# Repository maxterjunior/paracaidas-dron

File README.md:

# Paracaídas de Emergencia para DJI Matrice 400

Sistema autónomo que detecta la caída libre del dron con una IMU y despliega un paracaídas mediante un tubo de muelle. Funciona **independiente del flight controller**: tiene su propia batería, su MCU y su sensor.

<p align="center">

</p>
<p align="center"><sub>Izquierda: mecanismo en el <a href="https://claude.ai/artifact/HH7TuvKMzHhvBDsvPzRwz9">visor 3D</a>. Derecha: placa de control (render de KiCad).</sub></p>

| | |
|---|---|
| **Dron objetivo** | DJI Matrice 400: 9.74 kg con baterías, MTOW 15.8 kg |
| **MCU** | PIC18F25K22 (SSOP-28) con oscilador interno de 16 MHz sin PLL, 3.3 V |
| **IMU** | BMI088 (acelerómetro ±12 g + giróscopo ±1000 °/s) soldado en la placa, I²C: acel. 0x18 / giro 0x68 |
| **Actuador** | Solenoide 5 V que libera el pestillo de un tubo de muelle |
| **Mecanismo** | Tubo Ø100 × 280 mm con tapa articulada, modelo paramétrico OpenSCAD y [visor 3D](https://claude.ai/artifact/HH7TuvKMzHhvBDsvPzRwz9) |
| **Paracaídas** | Circular, ripstop nylon 30D, **Ø3.5 m**, 12 gajos, descenso ≤ 6 m/s a 16 kg |
| **Alimentación** | LiPo 1S 1000 mAh → interruptor MOSFET → LDO 3.3 V (XC6206) + boost 5.1 V (MT3608) |

## Estado

| Área | Estado |
|---|---|
| Investigación de módulos y paracaídas | ✅ Completa |
| Esquemático (KiCad 10, rev. v4, todo SMD) | ✅ Cableado, ERC limpio, campo LCSC en cada componente |
| PCB 2 capas 60 × 40 mm | ✅ Ruteado, planos de GND, DRC limpio, archivos JLCPCB listos |
| Firmware (MPLAB XC8) | 🚧 v0.1.0 escrita, sin compilar ni probar en hardware |
| Mecanismo (tubo de muelle) | 🚧 Modelo 3D y STL listos, sin interferencias; faltan medidas reales del solenoide y del montaje en el M400 |
| Canopia | ⏳ Pendiente (comprar o coser, ver `modulos.md`) |

## Cómo funciona

```
LiPo 1S ─Q3/SW1─┬─► XC6206 3.3V ─► PIC18F25K22 ◄─I²C─► BMI088
                │                       │
                └─► MT3608 5.1V ────────┼─► AO3400A ─► Solenoide ─► pestillo ─► muelle ─► paracaídas
                                        └─► LEDs / buzzer
```

1. El PIC lee el BMI088 a 500 Hz y filtra las señales con IIR de primer orden (solo aritmética entera, el PIC18 no tiene FPU).
2. Se **arma** solo en vuelo: cuando detecta la vibración de los motores durante 5 s. En tierra no dispara.
3. Armado, despliega si se cumple cualquiera de estos criterios: **caída libre** (|a| < 0.3 g durante 100 ms), **giro descontrolado** (|ω| > 250 °/s durante 300 ms) o **inclinación** (> 70° durante 500 ms).
4. Da dos pulsos de 300 ms al solenoide, que retrae el émbolo que bloquea la palanca del pestillo. La tapa se abre y el muelle expulsa el paracaídas en ~50–100 ms (ver [Mecanismo](#mecanismo)).
5. El pestillo retiene **sin energía**. Un reset nunca despliega por sí solo (R2 mantiene Q1 apagado), pero si el PIC se reinicia *durante* un despliegue, lo repite al arrancar.

Detalles en [`firmware/README.md`](firmware/README.md).

### Limitaciones conocidas

- **Altura mínima de despliegue: ~20–40 m.** Entre detección, expulsión e inflado se pierden 1.5–2.5 s.
- **La caída libre sola no basta.** Si falla un motor, el dron gira con los demás empujando y el acelerómetro no ve 0 g. Por eso el firmware también dispara por giro e inclinación. Falta un disparo manual por radio (RB2 libre) y calibrar los umbrales con vuelos reales.
- **No corta los motores.** El tubo debe expulsar hacia arriba, fuera del plano de las hélices.

## Estructura del repositorio

```
paracaidas-dron/
├── docs/
│   ├── esquematicos/esquematico.md   # Fuente de verdad: componentes, netlist pin a pin, notas
│   └── investigacion/modulos.md      # Selección de módulos, cálculo y construcción del paracaídas
├── hardware/
│   ├── paracaidas-matrice400/        # Proyecto KiCad 10 (.kicad_pro / .kicad_sch / .kicad_pcb)
│   │   ├── paracaidas.kicad_sym      # Símbolo propio (BMI088 en modo I2C)
│   │   ├── paracaidas.pretty/        # Footprint propio (buzzer MLT-9650)
│   │   └── jlcpcb/                   # Gerbers, BOM y CPL para pedir la placa armada
│   └── mecanismo/
│       ├── mecanismo.scad            # Modelo paramétrico OpenSCAD (tubo, tapa, pestillo, caja, adaptador)
│       ├── stl/                      # Piezas imprimibles exportadas
│       └── visor/                    # Visor 3D (three.js) generado desde los STL
├── firmware/                         # PIC18F25K22, MPLAB XC8 (ver firmware/README.md)
│   ├── src/                          # main, detector, configuración, placa
│   ├── lib/                          # HAL (tick, I2C, UART, ADC) y driver BMI088
│   └── test/                         # pruebas de la lógica de detección en la PC
├── CLAUDE.md                         # Guía para Claude Code
└── README.md
```

## Primeros pasos

### Abrir el hardware

1. Instala [KiCad 10](https://www.kicad.org/download/).
2. Abre `hardware/paracaidas-matrice400/paracaidas-matrice400.kicad_pro`.

Para verificar el diseño desde la línea de comandos:

```sh
KICAD="C:/Program Files/KiCad/10.0/bin/kicad-cli.exe"
cd hardware/paracaidas-matrice400

"$KICAD" sch erc paracaidas-matrice400.kicad_sch
"$KICAD" pcb drc --schematic-parity paracaidas-matrice400.kicad_pcb
```

### Firmware

```sh
cd firmware
make          # build/paracaidas.hex (MPLAB XC8)
make test     # lógica de detección en la PC (gcc)
```

- Programado con PICkit por el header ICSP **J2** (RB6/RB7).
- Log de estado por el header UART **J1** (RC6 TX / RC7 RX), 115200 8N1.
- Instrucciones, estados, LEDs y calibración en [`firmware/README.md`](firmware/README.md).

## Cambiar el diseño

[`docs/esquematicos/esquematico.md`](docs/esquematicos/esquematico.md) es la **fuente de verdad** de la conectividad. Las referencias coinciden 1:1 con el `.kicad_sch` y el `.kicad_pcb`.

Para cualquier cambio de conexiones:

1. Actualiza el documento **y** el esquemático, y corre el ERC.
2. Actualiza el PCB desde el esquemático (F8) y vuelve a rutear las redes afectadas.
3. Rellena las zonas (B) y corre el DRC con `--schematic-parity`.

Netclasses del PCB: `Default` 0.2 mm con 0.15 mm de separación (paso fino del SSOP-28 y del LGA-16) y `Power` 0.6 mm (+5V, VBAT, SW_NODE, SOL_DRV, BAT+). GND va por plano de cobre en ambas caras.

### Pedir la placa a JLCPCB

1. Sube `hardware/paracaidas-matrice400/jlcpcb/paracaidas-matrice400-gerbers.zip` (se genera junto con los gerbers y no se versiona; si no está, comprime la carpeta `gerbers/`).
2. En PCB Assembly sube `bom_jlcpcb.csv` y `cpl_jlcpcb.csv` (cara superior).
3. Revisa la rotación de los componentes en el visor antes de confirmar. Todos los componentes, incluidos los conectores, los monta JLCPCB.

Si cambias el PCB, vuelve a exportar gerbers, taladros y posiciones con `kicad-cli pcb export gerbers|drill|pos`.

## Mecanismo

Tubo de muelle montado sobre el dron con una placa adaptadora. **[Ver el modelo en 3D](https://claude.ai/artifact/HH7TuvKMzHhvBDsvPzRwz9)**: tiene animación del despliegue, vista en corte y el nombre de cada pieza al pasar el ratón.

| Pieza | Qué hace | Material |
|---|---|---|
| Tubo Ø105/Ø100 × 280 mm | Aloja ~1.6 L de paracaídas plegado | PETG impreso o tubo PVC 110 mm |
| Base | Encaje del tubo, asiento del resorte, paso central del cordón de anclaje | PETG |
| Pistón | Empuja el paracaídas | PETG |
| Resorte Ø90 mm | Comprimido a 45 mm en vuelo | Acero (comprado) |
| Tapa articulada | Se abre sobre su bisagra y queda unida al tubo; su pestaña tiene la ventana del pestillo | PETG |
| Collar | Bisagra, pivote de la palanca, guía del émbolo y repisa del solenoide | PETG |
| Palanca del pestillo | Su gancho entra en la ventana de la tapa | PETG o PA |
| Solenoide 5 V push-pull | El émbolo bloquea la palanca de costado | JF-0530B (comprado) |
| Caja electrónica | PCB 60 × 40 + LiPo 1S; tapa con agujeros sobre LEDs, buzzer, reset, J1 y J2 | PETG |
| Placa adaptadora | Une tubo y caja al dron | Aluminio 4 mm o PETG |

**Cómo traba:** la carga del resorte pasa a 2.7 mm del pivote de la palanca, así que el émbolo solo la bloquea de costado y le basta un solenoide pequeño. Sin energía, el muelle del solenoide deja el émbolo extendido y la tapa trabada. La boca del tubo queda ~273 mm por encima del plano de las hélices.

**Verificado con OpenSCAD:** ninguna pieza montada se cruza con otra. La tapa abre de 0° a 118° sin chocar, la palanca gira 22° libre con el émbolo retraído y queda bloqueada con el émbolo extendido.

**Antes de fabricar hay que medir:**

- El solenoide real (cuerpo, carrera, largo del émbolo): parámetros `sol_*`.
- El punto de montaje superior del M400: el patrón de tornillos de la placa (`montaje_*`) y la envolvente del dron son provisionales.
- La fuerza del resorte: debe sacar ~0.6 kg por encima de las hélices. Probar en banco.

> El cordón de anclaje se ata a la **estructura del dron**, no a piezas impresas: el choque de apertura con 16 kg es de cientos de newtons.

### Exportar las piezas

Instala [OpenSCAD](https://openscad.org/downloads.html) y exporta cada pieza:

```sh
cd hardware/mecanismo
openscad -D 'pieza="tapa"' -o stl/tapa.stl mecanismo.scad
```

Piezas imprimibles: `base`, `tubo`, `piston`, `tapa`, `collar`, `palanca`, `caja`, `tapa_caja`, `adaptador`. Las medidas están como parámetros al inicio del `.scad`. Los STL salen en posición de montaje, así que hay que orientarlos en el slicer. El tubo necesita ~290 mm de altura de impresión; si no alcanza, usa PVC.

### Visor 3D

`hardware/mecanismo/visor/index.html` se abre con doble clic, sin servidor. Carga las piezas de `piezas.js`, que contiene los STL de OpenSCAD en base64. Si cambias el `.scad`, regenera ese archivo:

```sh
python hardware/mecanismo/visor/empaquetar.py "C:/Program Files/OpenSCAD/openscad.com"
```

## Paracaídas

El dimensionamiento completo, el patrón de gajos, la costura y los proveedores (Fruity Chutes, Mars Parachutes, modelos para 15–16 kg) están en [`docs/investigacion/modulos.md`](docs/investigacion/modulos.md#paracaídas--canopia-y-mecanismo-de-despliegue).

```
Área = 2·m·g / (Cd·ρ·v²) = (2 × 16 × 9.81) / (0.75 × 1.225 × 6²) ≈ 9.5 m²  →  Ø3.5 m
```

> Los paracaídas de Ø1.2 m que venden en AliExpress son para drones de 2–4 kg. Con el M400 darían 14–17 m/s de descenso, el equivalente a soltarlo desde 10–15 m.

## Commits

Este repo usa [Conventional Commits](https://www.conventionalcommits.org/es/v1.0.0/) con emoji y la descripción en español:

```
feat(hardware): ✨ esquemático cableado sin r5/r6 y pcb ruteado con plano de gnd
```

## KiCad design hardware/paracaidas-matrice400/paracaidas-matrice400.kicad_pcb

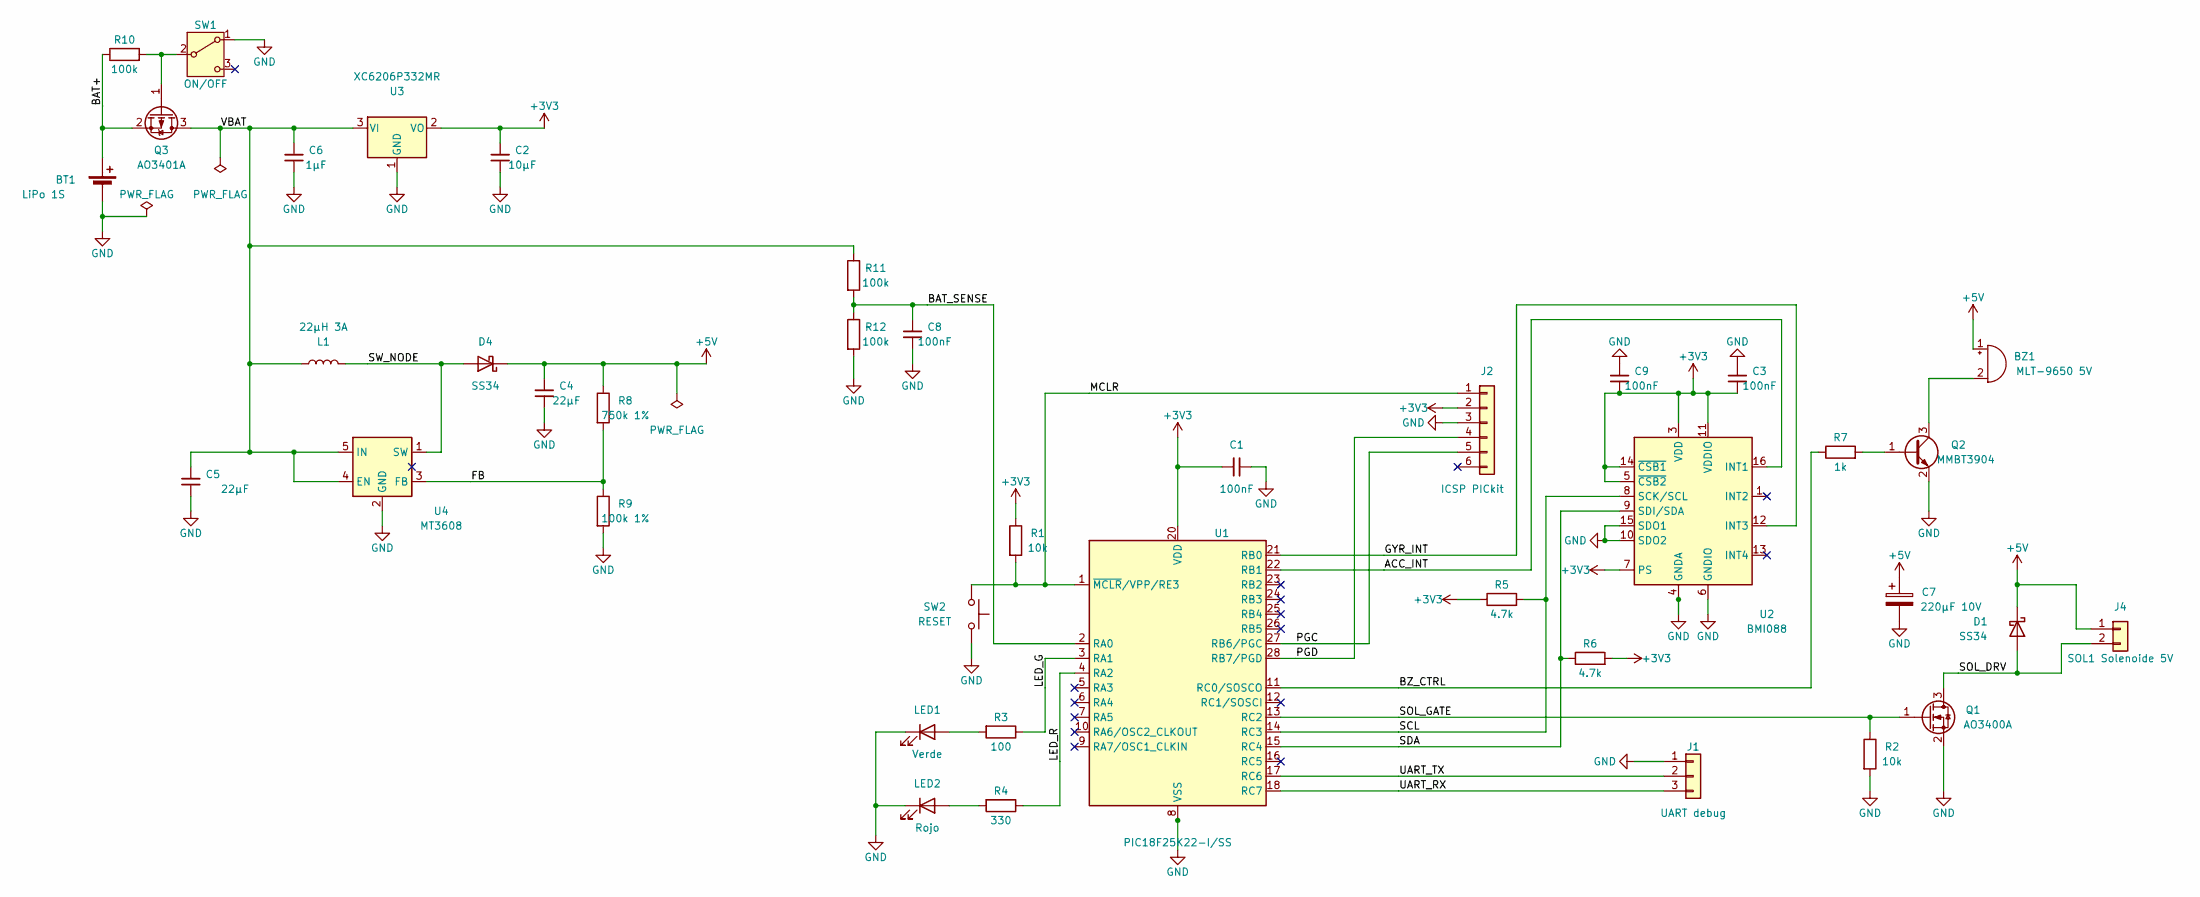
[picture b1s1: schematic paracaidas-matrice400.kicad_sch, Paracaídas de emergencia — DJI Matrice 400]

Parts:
BT1: LiPo 1S; JST_PH_S2B-PH-SM4-TB_1x02-1MP_P2.00mm_Horizontal; LCSC C295747
BZ1: MLT-9650 5V; Buzzer_MLT-9650; LCSC C96127
C1, C3, C8, C9: 100nF; C_0603_1608Metric; LCSC C14663
C2: 10µF; C_0805_2012Metric; LCSC C15850
C4, C5: 22µF; C_0805_2012Metric; LCSC C45783
C6: 1µF; C_0603_1608Metric; LCSC C15849
C7: 220µF 10V; CP_Elec_6.3x5.4; LCSC C72494
D1, D4: SS34; D_SMA; LCSC C8678
J1: UART debug; PinHeader_1x03_P2.54mm_Vertical_SMD_Pin1Left; LCSC C41417360
J2: ICSP PICkit; PinHeader_1x06_P2.54mm_Vertical_SMD_Pin1Right; LCSC C41417363
J4: SOL1 Solenoide 5V; JST_PH_S2B-PH-SM4-TB_1x02-1MP_P2.00mm_Horizontal; LCSC C295747
L1: 22µH 3A; L_Changjiang_FXL0630; LCSC C177244
LED1: Verde; LED_0603_1608Metric; LCSC C12624
LED2: Rojo; LED_0603_1608Metric; LCSC C2286
Q1: AO3400A; SOT-23; LCSC C20917
Q2: MMBT3904; SOT-23; LCSC C20526
Q3: AO3401A; SOT-23; LCSC C15127
R1, R2: 10k; R_0603_1608Metric; LCSC C25804
R3: 100; R_0603_1608Metric; LCSC C22775
R4: 330; R_0603_1608Metric; LCSC C23138
R5, R6: 4.7k; R_0603_1608Metric; LCSC C23162
R7: 1k; R_0603_1608Metric; LCSC C21190
R8: 750k 1%; R_0603_1608Metric; LCSC C23240
R9: 100k 1%; R_0603_1608Metric; LCSC C25803
R10, R11, R12: 100k; R_0603_1608Metric; LCSC C25803
SW1: ON/OFF; SW_SPDT_Shouhan_MSK12C02; LCSC C431540
SW2: RESET; SW_Push_1P1T_XKB_TS-1187A; LCSC C318884
U1: PIC18F25K22-I/SS; SSOP-28_5.3x10.2mm_P0.65mm; LCSC C51680
U2: BMI088; Bosch_LGA-16_4.5x3mm_P0.5mm_LayoutBorder7x1y_ClockwisePinNu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; LCSC C194919
U3: XC6206P332MR; SOT-23-3; LCSC C5446
U4: MT3608; SOT-23-6; LCSC C84817

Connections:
+3V3: C1.1, C2.1, C3.2, C9.2, J2.2, R1.1, R5.1, R6.2, U1.20 (VDD), U2.3 (VDD), U2.5 (~CSB2), U2.7 (PS), U2.11 (VDDIO), U2.14 (~CSB1), U3.2 (VO)
+5V: BZ1.1 (+), C4.1, C7.1, D1.1 (K), D4.1 (K), J4.1, R8.1
/ACC_INT: U1.22 (RB1), U2.16 (INT1)
/BAT+: BT1.1 (+), Q3.2 (S), R10.1
/BAT_SENSE: C8.1, R11.2, R12.1, U1.2 (RA0)
/BZ_CTRL: R7.1, U1.11 (RC0/SOSCO)
/FB: R8.2, R9.1, U4.3 (FB)
/GYR_INT: U1.21 (RB0), U2.12 (INT3)
/LED_G: R3.1, U1.3 (RA1)
/LED_R: R4.1, U1.4 (RA2)
/MCLR: J2.1, R1.2, SW2.1, U1.1 (~MCLR/VPP/RE3)
/PGC: J2.5, U1.27 (RB6/PGC)
/PGD: J2.4, U1.28 (RB7/PGD)
/SCL: R5.2, U1.14 (RC3), U2.8 (SCK/SCL)
/SDA: R6.1, U1.15 (RC4), U2.9 (SDI/SDA)
/SOL_DRV: D1.2 (A), J4.2, Q1.3 (D)
/SOL_GATE: Q1.1 (G), R2.1, U1.13 (RC2)
/SW_NODE: D4.2 (A), L1.2, U4.1 (SW)
/UART_RX: J1.3, U1.18 (RC7)
/UART_TX: J1.2, U1.17 (RC6)
/VBAT: C5.1, C6.1, L1.1, Q3.3 (D), R11.1, U3.3 (VI), U4.4 (EN), U4.5 (IN)
GND: BT1.2 (-), C1.2, C2.2, C3.1, C4.2, C5.2, C6.2, C7.2, C8.2, C9.1, J1.1, J2.3, LED1.1 (K), LED2.1 (K), Q1.2 (S), Q2.2 (E), R2.2, R9.2, R12.2, SW1.1 (A), SW2.2, U1.8 (VSS), U1.19 (VSS), U2.2 (GNDA), U2.4 (GNDA), U2.6 (GNDIO), U2.10 (SDO2), U2.15 (SDO1), U3.1 (GND), U4.2 (GND)
unnamed: BZ1.2 (-), Q2.3 (C)
unnamed: LED1.2 (A), R3.2
unnamed: LED2.2 (A), R4.2
unnamed: Q2.1 (B), R7.2
unnamed: Q3.1 (G), R10.2, SW1.2 (B)

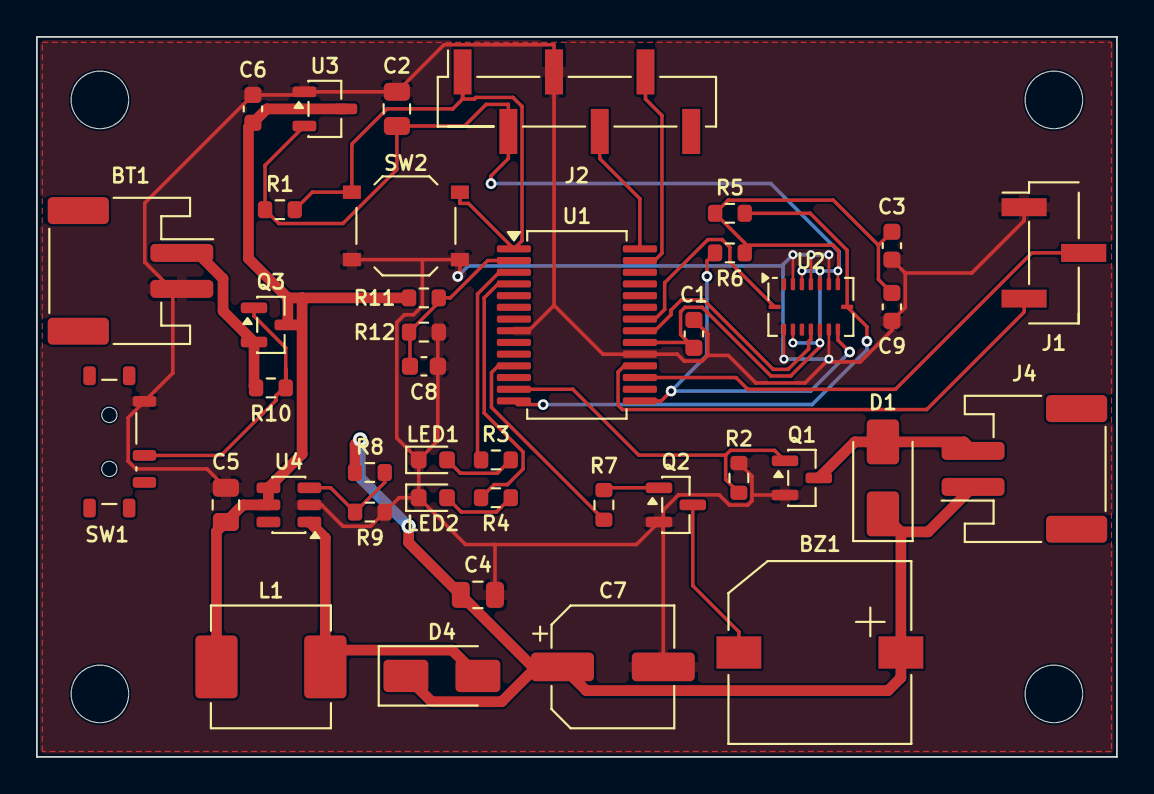
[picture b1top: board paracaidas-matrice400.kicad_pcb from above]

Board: 2 copper layers, 60.0 x 40.0 mm, 44 parts (0 on the bottom side), 27 nets.

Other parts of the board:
H1, H2, H3, H4: M3; MountingHole_3.2mm_M3

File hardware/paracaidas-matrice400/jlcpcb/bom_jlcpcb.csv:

Comment,Designator,Footprint,LCSC Part #
LiPo 1S,BT1,JST_PH_S2B-PH-SM4-TB_1x02-1MP_P2.00mm_Horizontal,C295747
MLT-9650 5V,BZ1,Buzzer_MLT-9650,C96127
100nF,"C1,C3,C8,C9",C_0603_1608Metric,C14663
10µF,C2,C_0805_2012Metric,C15850
22µF,"C4,C5",C_0805_2012Metric,C45783
1µF,C6,C_0603_1608Metric,C15849
220µF 10V,C7,CP_Elec_6.3x5.4,C72494
SS34,"D1,D4",D_SMA,C8678
UART debug,J1,PinHeader_1x03_P2.54mm_Vertical_SMD_Pin1Left,C41417360
ICSP PICkit,J2,PinHeader_1x06_P2.54mm_Vertical_SMD_Pin1Right,C41417363
SOL1 Solenoide 5V,J4,JST_PH_S2B-PH-SM4-TB_1x02-1MP_P2.00mm_Horizontal,C295747
22µH 3A,L1,L_Changjiang_FXL0630,C177244
Verde,LED1,LED_0603_1608Metric,C12624
Rojo,LED2,LED_0603_1608Metric,C2286
AO3400A,Q1,SOT-23,C20917
MMBT3904,Q2,SOT-23,C20526
AO3401A,Q3,SOT-23,C15127
10k,"R1,R2",R_0603_1608Metric,C25804
100,R3,R_0603_1608Metric,C22775
330,R4,R_0603_1608Metric,C23138
4.7k,"R5,R6",R_0603_1608Metric,C23162
1k,R7,R_0603_1608Metric,C21190
750k 1%,R8,R_0603_1608Metric,C23240
100k 1%,R9,R_0603_1608Metric,C25803
100k,"R10,R11,R12",R_0603_1608Metric,C25803
ON/OFF,SW1,SW_SPDT_Shouhan_MSK12C02,C431540
RESET,SW2,SW_Push_1P1T_XKB_TS-1187A,C318884
PIC18F25K22-I/SS,U1,SSOP-28_5.3x10.2mm_P0.65mm,C51680
BMI088,U2,Bosch_LGA-16_4.5x3mm_P0.5mm_LayoutBorder7x1y_ClockwisePinNumbering,C194919
XC6206P332MR,U3,SOT-23-3,C5446
MT3608,U4,SOT-23-6,C84817

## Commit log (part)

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2026-03-30 Refactor code structure for improved readability and maintainability
2026-05-16 Add lock file for paracaidas-matrice400 schematic with user and hostname information
2026-05-17 Remove lock file for paracaidas-matrice400 schematic
